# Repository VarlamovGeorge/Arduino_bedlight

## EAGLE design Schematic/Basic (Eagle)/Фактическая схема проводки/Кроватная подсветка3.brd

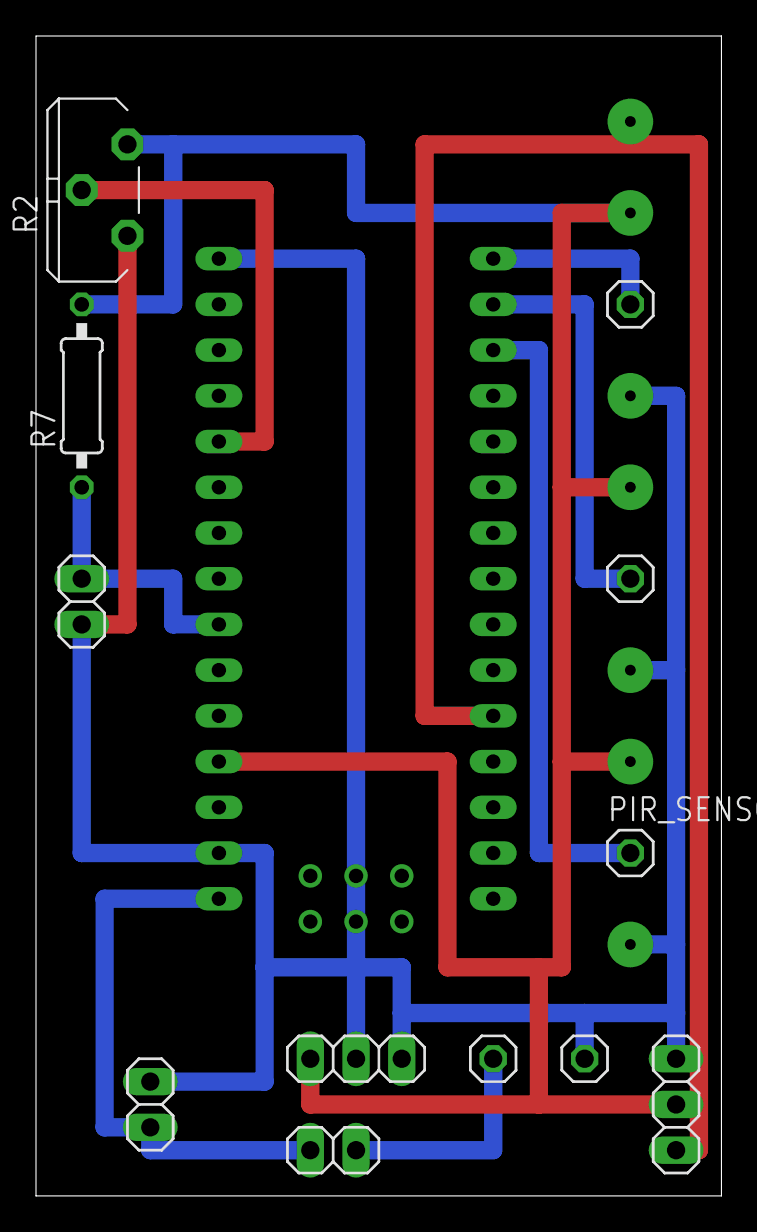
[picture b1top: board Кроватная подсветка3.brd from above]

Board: 2 copper layers, 38.1 x 64.4 mm, 13 parts (0 on the bottom side), 11 nets.

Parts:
DC_ADAPTER(12V): 1X02
LED_GND: 1X01
LED_SUPPLY: 1X01
LIGHT_SENSOR: 1X02
PIR_SENSOR_1, PIR_SENSOR_2, PIR_SENSOR_3: 1X01
R2: PT-10S
R7: 20k; 0207/10
RELAY: 1X03
TOUCHSENSOR: 1X03
TO_RELAY: 1X02
U$1: NANO

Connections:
+5V: R2.2, R7.2, RELAY.1, TOUCHSENSOR.2, U$1.5V
AGND: DC_ADAPTER(12V).2, LED_GND.1, LIGHT_SENSOR.1, R2.1, RELAY.3, TOUCHSENSOR.1, U$1.GND
unnamed: LIGHT_SENSOR.2, R7.1, U$1.A5
unnamed: PIR_SENSOR_1.1, U$1.D12
unnamed: RELAY.2, U$1.D13
unnamed: TOUCHSENSOR.3, U$1.D2
unnamed: LED_SUPPLY.1, TO_RELAY.2
unnamed: DC_ADAPTER(12V).1, TO_RELAY.1, U$1.RAW
unnamed: PIR_SENSOR_2.1, U$1.D11
unnamed: PIR_SENSOR_3.1, U$1.D10
unnamed: R2.3, U$1.A1

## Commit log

2019-03-16 Docs, 3d-model, shematics
2019-03-16 First draft
    Light-sensor connected to A2. Photoresisrot is used like a bottom shoulder of voltage devider. Top shoulder - 560k. Threshold - 200 (0-abs light, 1023-abs darkness). Output logic on pin 13.
2019-03-16 Version 0.2
    Code made prettier. UART is used only on switch deblight (1/0 comes to relay only in moment of changing state).
2019-03-16 v1.0
    Added while-loop, working only on dark. Added #define-block.
2019-03-16 v1.1
    Added falling-interrupt on D2 to switch on the light.
2019-03-16 v1.2
    Light sensor connected to A5 due to schematic changes.
2019-03-16 v1.3 stable
    Added potentiometr for manual changing the threshold. Interrupt uses additional delay.
2019-03-16 v1.4 stable
    Added software protection from contact bounce - delay between switching after pressing the button.
2019-03-16 v2.0 stable
    MOSFET added (LUT).
2019-03-16 v2.1
    Bright changing changes in real-time.
2019-03-16 v2.2
2019-03-16 v2.3 stable
    Diod 13 showing the threshold excess
2019-03-17 v2.4 stable
    Added manLightDur - max working duration. Button works only in the dark. Light doesnt turn off after lightDur if motion detected. Sketch replaced to homonymous folder
